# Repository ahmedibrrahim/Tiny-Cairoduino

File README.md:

# Tiny-Cairoduino
Tiny-Ciaroduino is a small-sized Development board based on the beautiful ATtiny85 chip from Atmel.

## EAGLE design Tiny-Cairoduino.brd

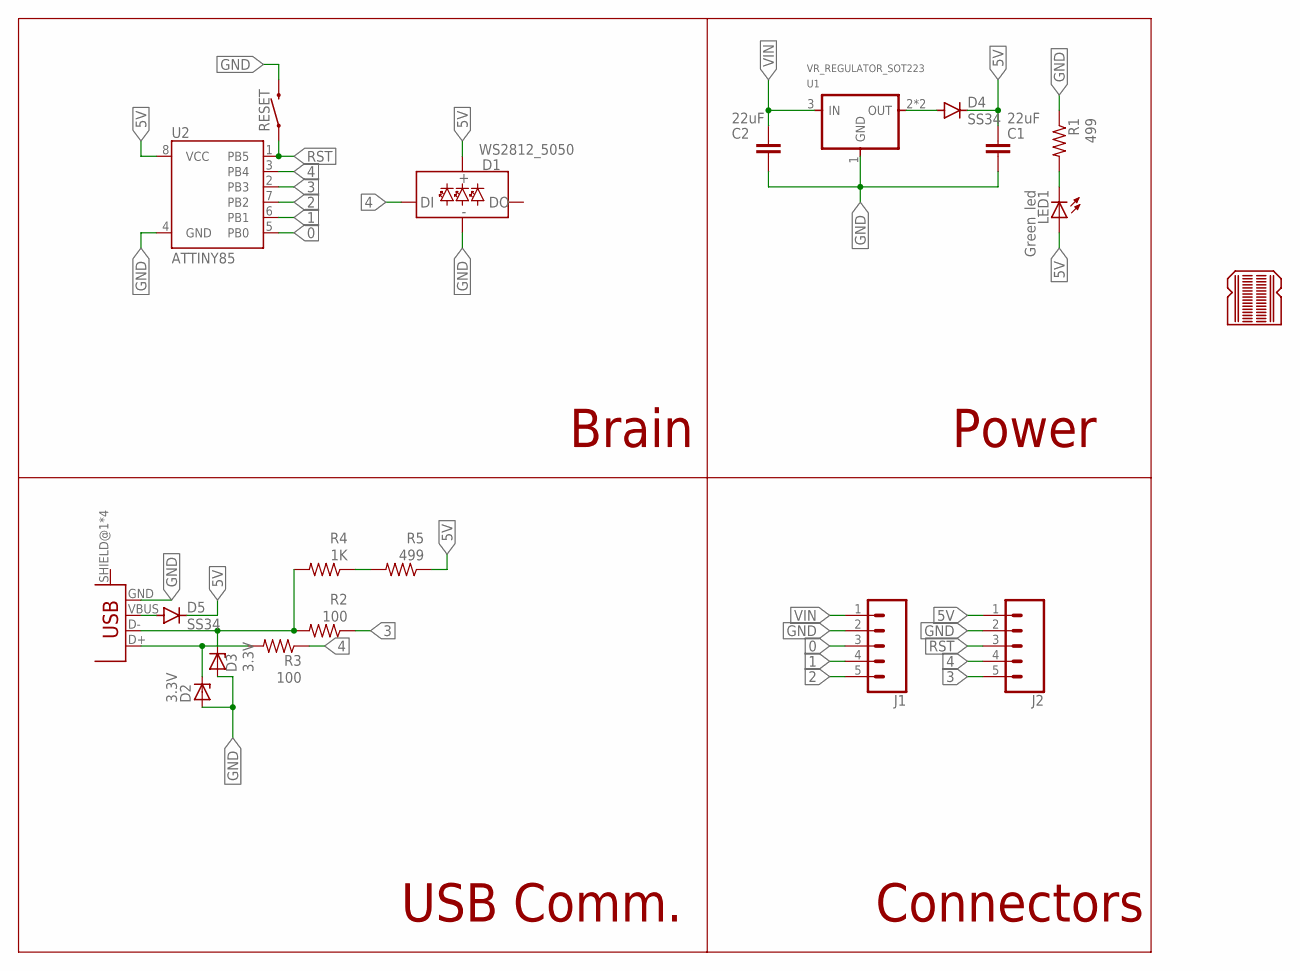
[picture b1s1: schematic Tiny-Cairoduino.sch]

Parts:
C1, C2: 22uF; 0805
D1: WS2812_5050; WS2812-5X5-4PIN
D2, D3: 3.3V; SOD123
D4, D5: SS34; DO-214AC
J1, J2: CONN_05; 1X05
LED1: Green_led; CHIP-LED0805
LOGO1: BREADBOARD_PATTERN; BREADBOARD_SPACING
R1, R5: 499; R1206FAB
R2, R3: 100; R1206FAB
R4: 1K; R1206FAB
RESET: MOMENTARY-SWITCH-SPST-SMD-6.0X3.5MM; TACTILE_SWITCH_SMD_6.0X3.5MM
U1: VR_REGULATOR_SOT223; SOT223
U2: ATTINY85
U$2: CONN_USB_MINIB; USB_MINIB

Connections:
0: J1.3, U2.5 (PB0)
1: J1.4, U2.6 (PB1)
2: J1.5, U2.7 (PB2)
3: J2.5, R2.1, U2.2 (PB3)
4: D1.DI, J2.4, R3.1, U2.3 (PB4)
5V: C1.1, D1.VCC, D4.C, D5.C, J2.1, LED1.A, R5.1, U2.8 (VCC)
GND: C1.2, C2.2, D1.GND, D2.ANODE, D3.ANODE, J1.2, J2.2, R1.1, RESET.2, U1.1 (GND), U2.4 (GND), U$2.GND
unnamed: LED1.C, R1.2
unnamed: D5.A, U$2.VBUS
unnamed: R4.1, R5.2
unnamed: D3.CATHODE, R2.2, R4.2, U$2.D-
unnamed: D2.CATHODE, R3.2, U$2.D+
unnamed: D4.A, U1.2 (OUT), U1.4 (OUT)
RST: J2.3, RESET.1, U2.1 (PB5)
VIN: C2.1, J1.1, U1.3 (IN)

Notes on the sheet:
USB Comm.
Power
Brain
Connectors

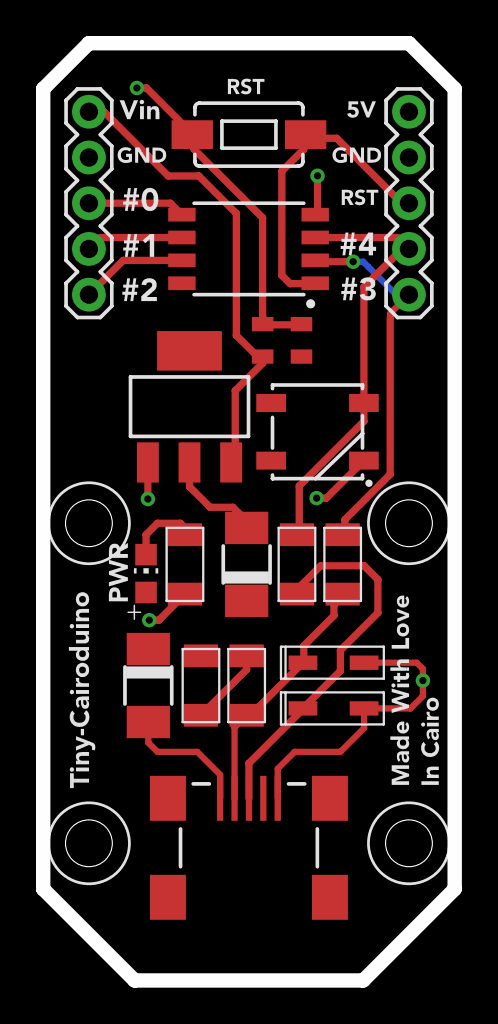
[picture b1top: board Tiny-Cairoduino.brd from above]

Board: 2 copper layers, 22.9 x 52.1 mm, 21 parts (1 on the bottom side), 15 nets.

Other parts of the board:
U$1: OSHW-LOGO-L

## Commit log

2022-01-31 Uploading source files

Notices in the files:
parts and their libraries:
SparkFun-Capacitors: Licensing: Creative Commons ShareAlike 4.0 International - https://creativecommons.org/licenses/by-sa/4.0
